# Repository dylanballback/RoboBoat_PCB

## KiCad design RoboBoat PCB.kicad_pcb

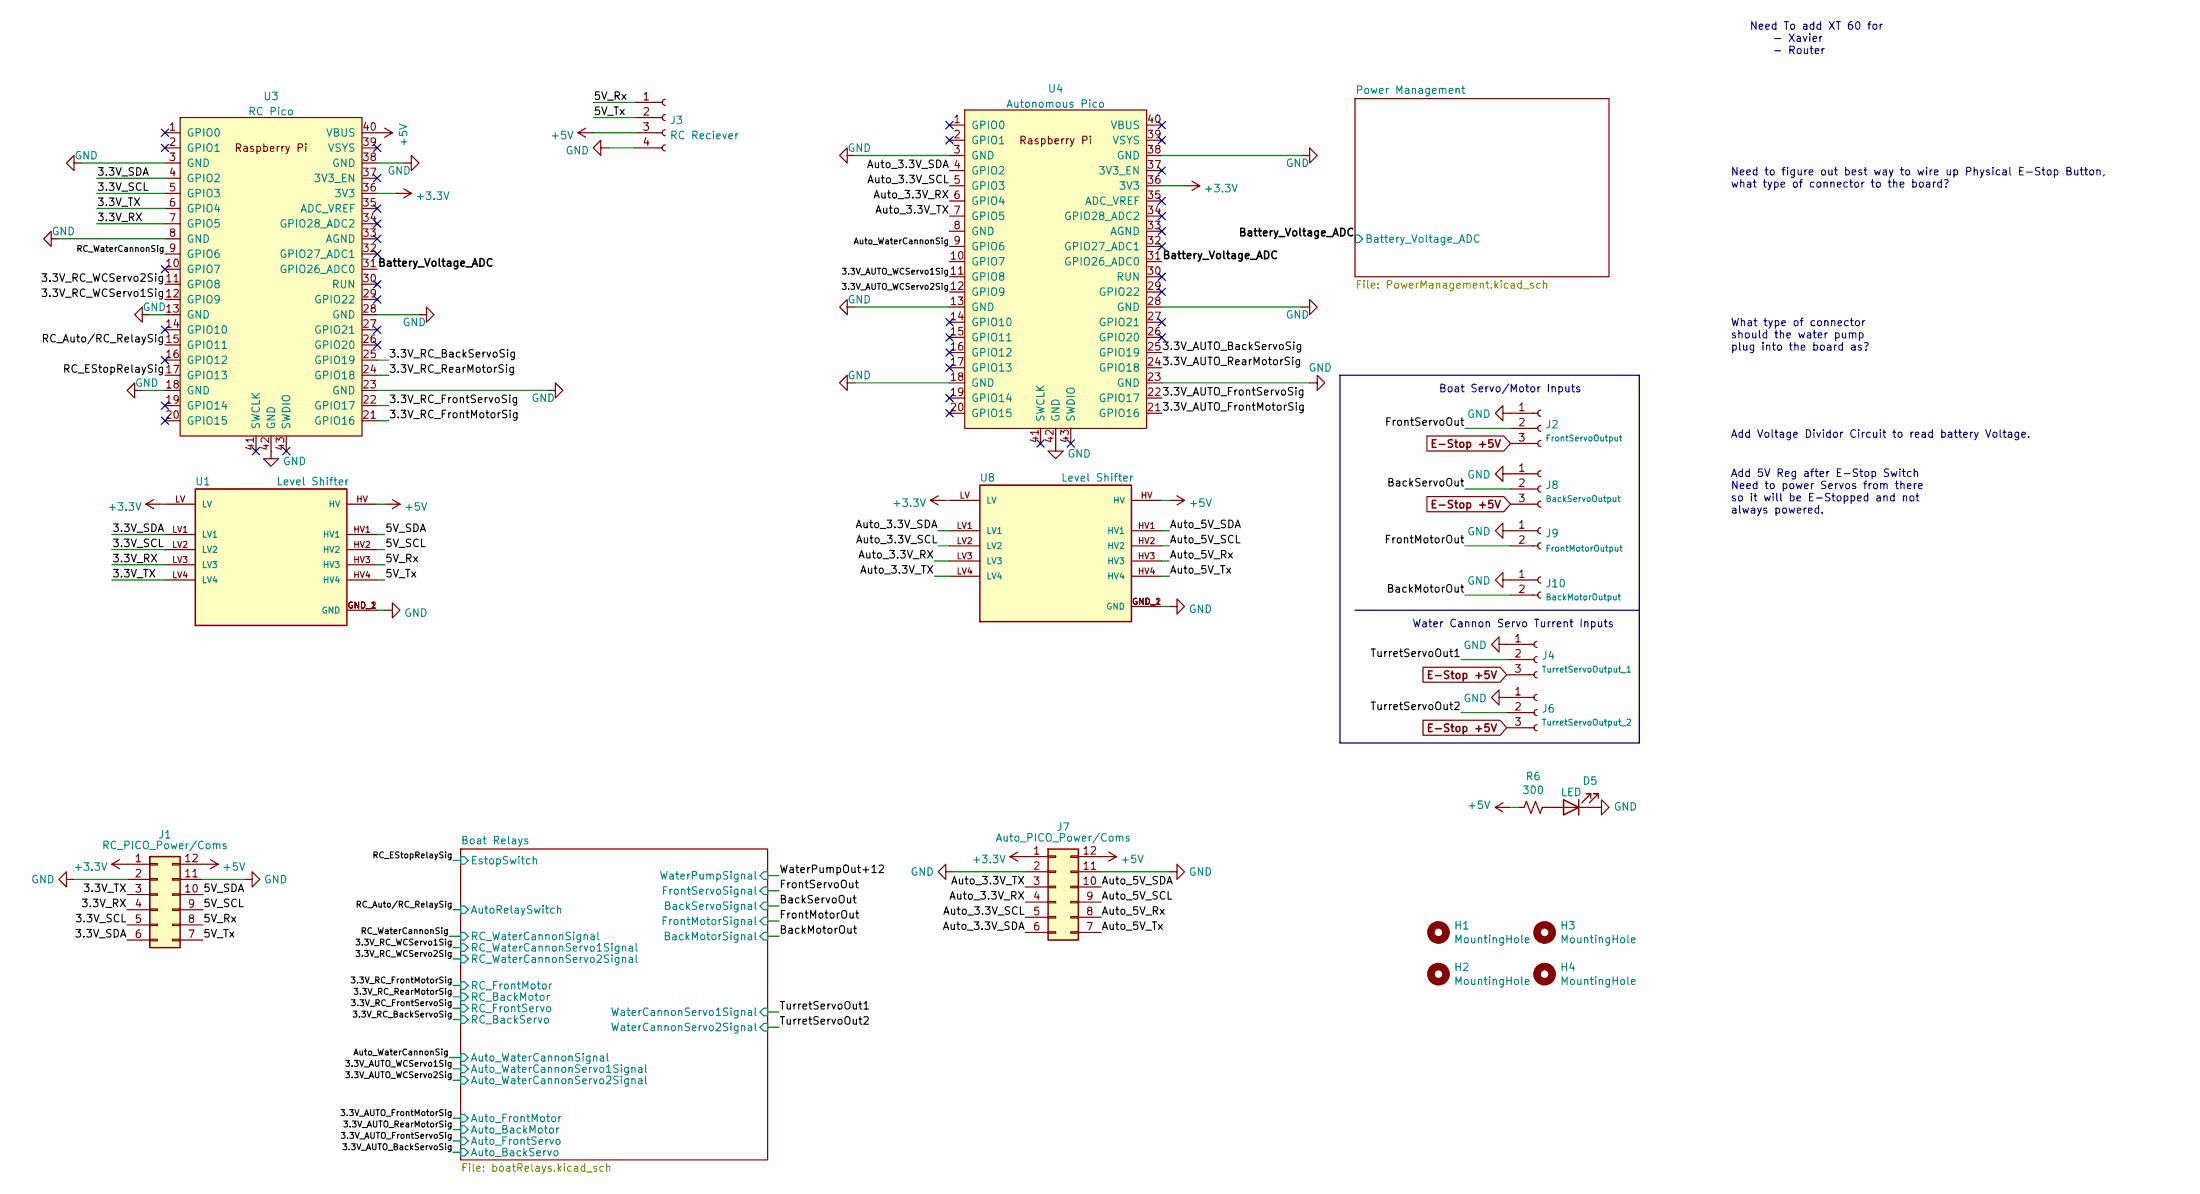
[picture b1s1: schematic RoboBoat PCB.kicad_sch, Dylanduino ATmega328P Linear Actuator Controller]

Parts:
D5: LED; LED_0402_1005Metric_Pad0.77x0.64mm_HandSolder
H1, H2, H3, H4: MountingHole; MountingHole_5.3mm_M5
J1: RC_PICO_Power/Coms; PinSocket_2x06_P2.54mm_Vertical
J2: FrontServoOutput; PinHeader_1x03_P2.54mm_Vertical
J3: RC Reciever; PinHeader_1x04_P2.54mm_Vertical
J4: TurretServoOutput_1; PinHeader_1x03_P2.54mm_Vertical
J6: TurretServoOutput_2; PinHeader_1x03_P2.54mm_Vertical
J7: Auto_PICO_Power/Coms; PinSocket_2x06_P2.54mm_Vertical
J8: BackServoOutput; PinHeader_1x03_P2.54mm_Vertical
J9: FrontMotorOutput; PinSocket_1x02_P2.54mm_Vertical
J10: BackMotorOutput; PinSocket_1x02_P2.54mm_Vertical
R6: 300; R_0805_2012Metric_Pad1.20x1.40mm_HandSolder
U1, U8: Level Shifter; CONV_BOB-12009; PARTREV 01
U3: RC Pico; RPi_Pico_SMD_TH
U4: Autonomous Pico; RPi_Pico_SMD_TH

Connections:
+3V3: J1.1, J7.1, U1.LV, U3.36 (3V3), U4.36 (3V3), U8.LV
+5V: J1.12, J3.3, J7.12, R6.2, U1.HV, U3.40 (VBUS), U8.HV; also elsewhere on the board
/3.3V_AUTO_BackServoSig: U4.25 (GPIO19); also elsewhere on the board
/3.3V_AUTO_FrontMotorSig: U4.21 (GPIO16); also elsewhere on the board
/3.3V_AUTO_FrontServoSig: U4.22 (GPIO17); also elsewhere on the board
/3.3V_AUTO_RearMotorSig: U4.24 (GPIO18); also elsewhere on the board
/3.3V_AUTO_WCServo1Sig: U4.11 (GPIO8); also elsewhere on the board
/3.3V_AUTO_WCServo2Sig: U4.12 (GPIO9); also elsewhere on the board
/3.3V_RC_BackServoSig: U3.25 (GPIO19); also elsewhere on the board
/3.3V_RC_FrontMotorSig: U3.21 (GPIO16); also elsewhere on the board
/3.3V_RC_FrontServoSig: U3.22 (GPIO17); also elsewhere on the board
/3.3V_RC_RearMotorSig: U3.24 (GPIO18); also elsewhere on the board
/3.3V_RC_WCServo1Sig: U3.12 (GPIO9); also elsewhere on the board
/3.3V_RC_WCServo2Sig: U3.11 (GPIO8); also elsewhere on the board
/3.3V_RX: J1.4, U1.LV3, U3.7 (GPIO5)
/3.3V_SCL: J1.5, U1.LV2, U3.5 (GPIO3)
/3.3V_SDA: J1.6, U1.LV1, U3.4 (GPIO2)
/3.3V_TX: J1.3, U1.LV4, U3.6 (GPIO4)
/5V_Rx: J1.8, J3.1, U1.HV3
/5V_SCL: J1.9, U1.HV2
/5V_SDA: J1.10, U1.HV1
/5V_Tx: J1.7, J3.2, U1.HV4
/Auto_3.3V_RX: J7.4, U4.6 (GPIO4), U8.LV3
/Auto_3.3V_SCL: J7.5, U4.5 (GPIO3), U8.LV2
/Auto_3.3V_SDA: J7.6, U4.4 (GPIO2), U8.LV1
/Auto_3.3V_TX: J7.3, U4.7 (GPIO5), U8.LV4
/Auto_5V_Rx: J7.8, U8.HV3
/Auto_5V_SCL: J7.9, U8.HV2
/Auto_5V_SDA: J7.10, U8.HV1
/Auto_5V_Tx: J7.7, U8.HV4
/Auto_WaterCannonSig: U4.9 (GPIO6); also elsewhere on the board
/BackMotorOut: J10.2; also elsewhere on the board
/BackServoOut: J8.2; also elsewhere on the board
/Battery_Voltage_ADC: U3.31 (GPIO26_ADC0), U4.31 (GPIO26_ADC0); also elsewhere on the board
/FrontMotorOut: J9.2; also elsewhere on the board
/FrontServoOut: J2.2; also elsewhere on the board
/RC_Auto/RC_RelaySig: U3.15 (GPIO11); also elsewhere on the board
/RC_EStopRelaySig: U3.17 (GPIO13); also elsewhere on the board
/RC_WaterCannonSig: U3.9 (GPIO6); also elsewhere on the board
/TurretServoOut1: J4.2; also elsewhere on the board
/TurretServoOut2: J6.2; also elsewhere on the board
E-Stop +5V: J2.3, J4.3, J6.3, J8.3; also elsewhere on the board
unnamed: D5.2 (A), R6.1

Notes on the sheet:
Need To add XT 60 for - Xavier - Router
Add Voltage Dividor Circuit to read battery Voltage.
Need to figure out best way to wire up Physical E-Stop Button, what type of connector to the board?
Boat Servo/Motor Inputs
What type of connector should the water pump plug into the board as?
Water Cannon Servo Turrent Inputs
Add 5V Reg after E-Stop Switch Need to power Servos from there so it will be E-Stopped and not always powered.

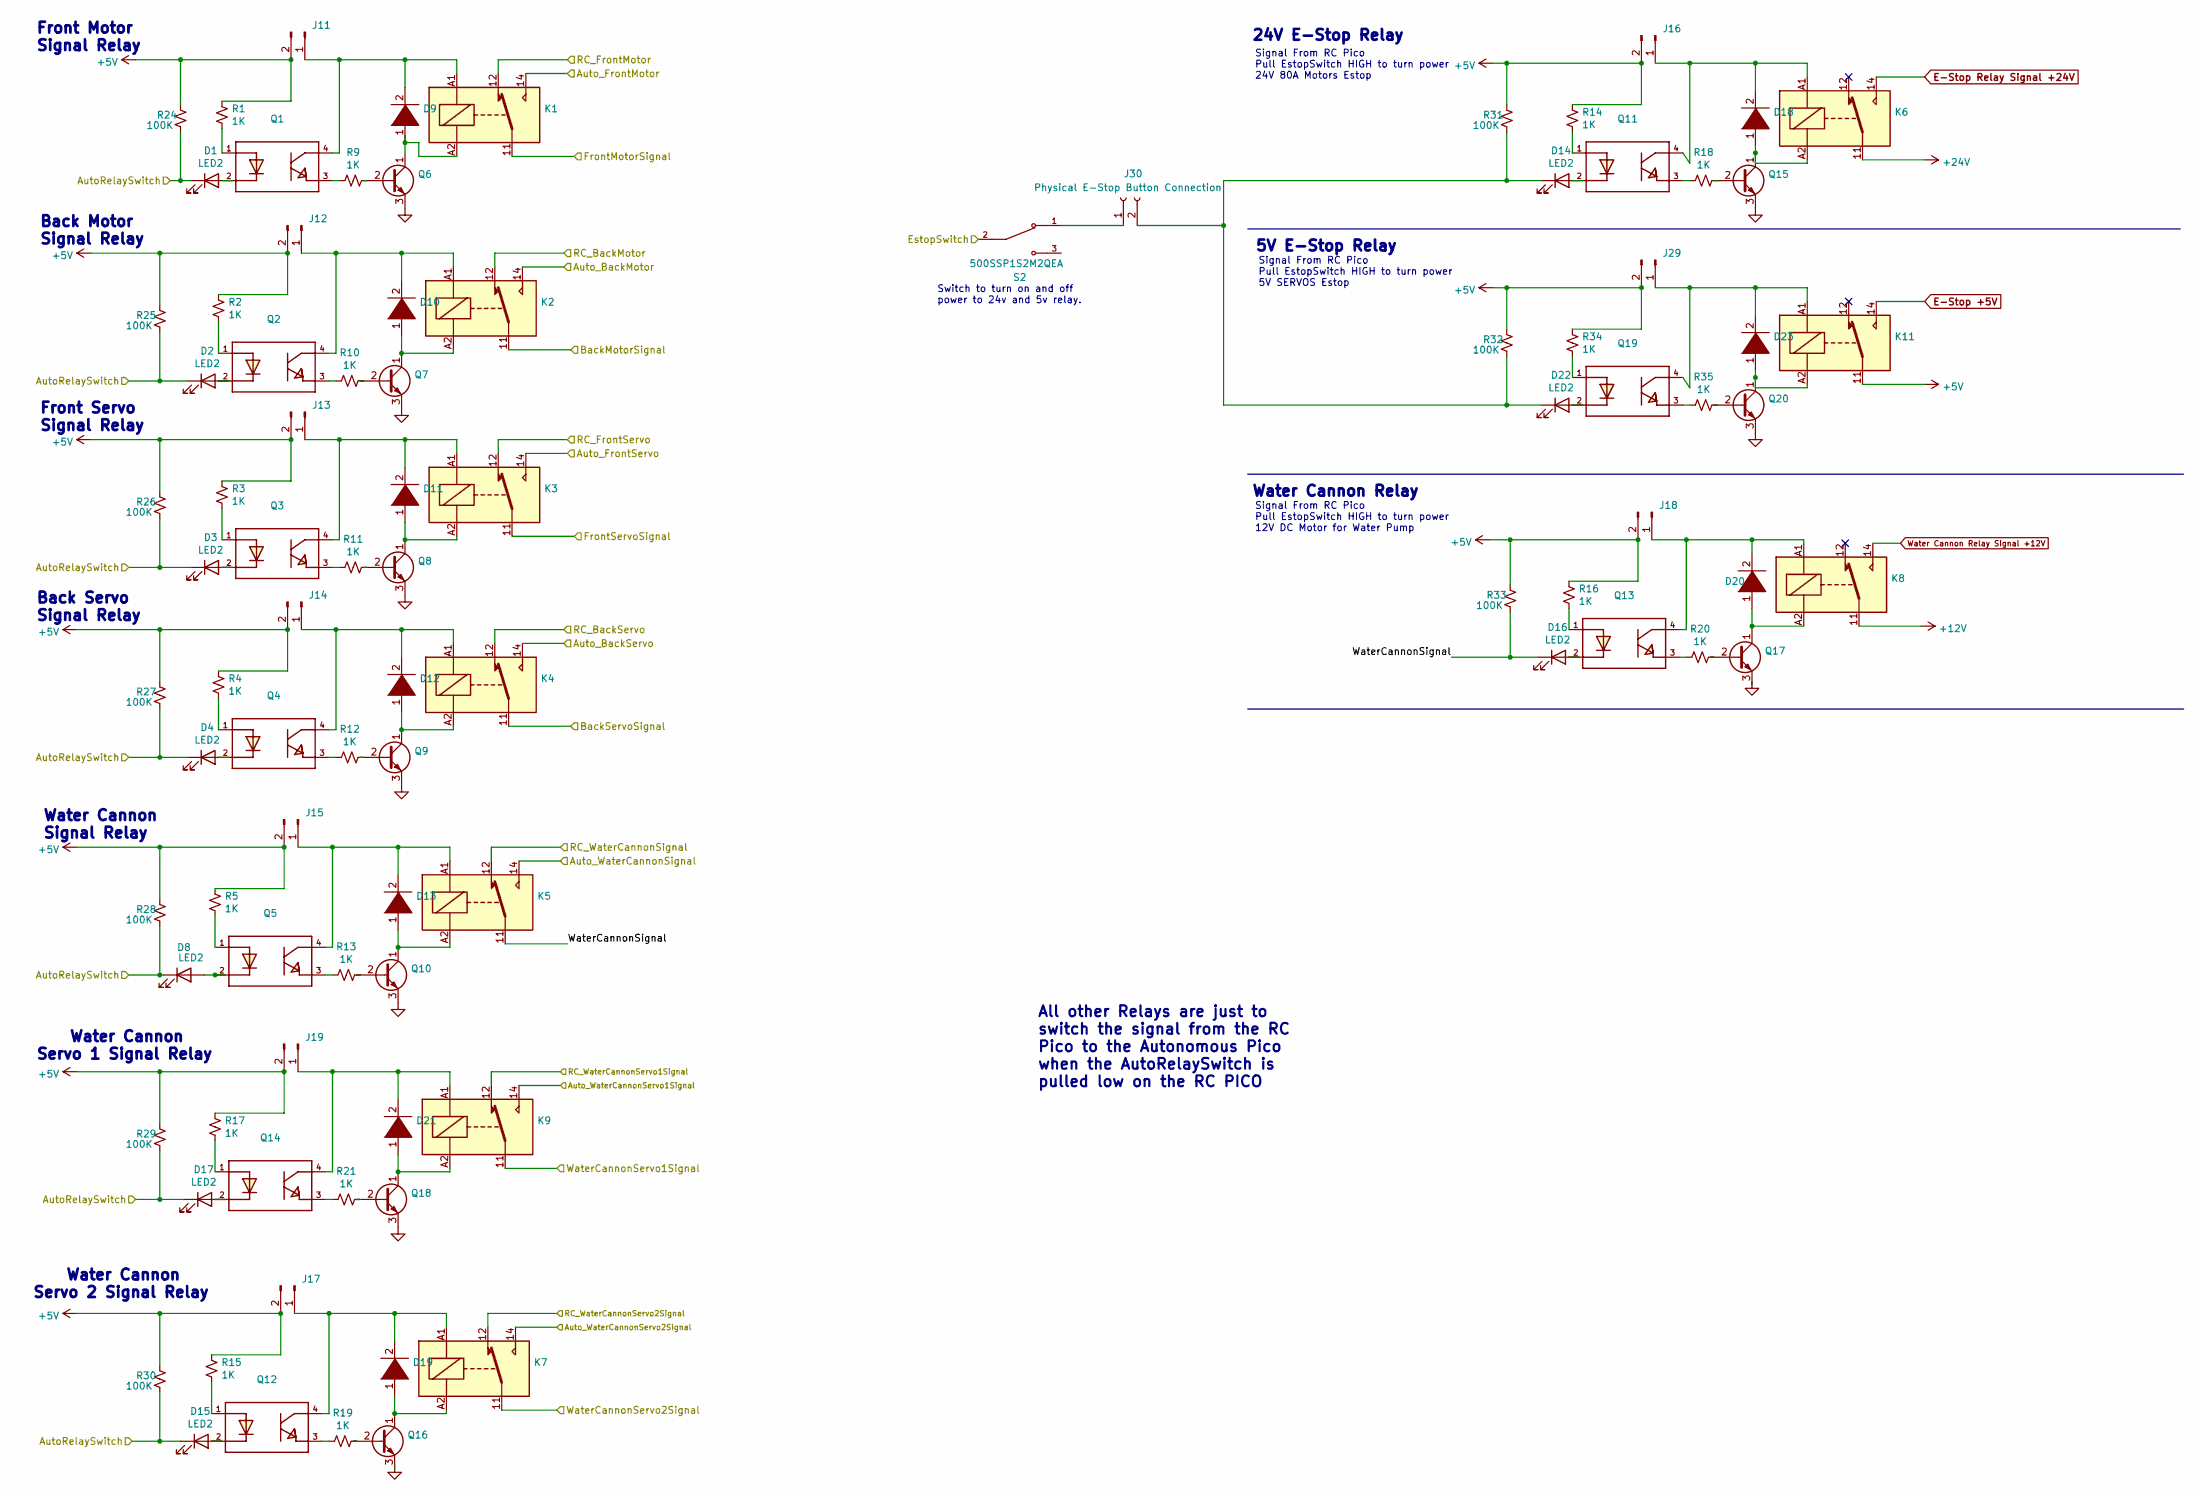
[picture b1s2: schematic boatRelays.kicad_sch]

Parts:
D1, D2, D3, D4, D8, D14, D15, D16, D17, D22: LED2; LED_0402_1005Metric_Pad0.77x0.64mm_HandSolder
D9, D10, D11, D12, D13, D18, D19, D20, D21, D23: D_1210_3225Metric_Pad1.42x2.65mm_HandSolder
J11, J12, J13, J14, J15, J16, J17, J18, J19, J29: PinHeader_1x02_P2.54mm_Vertical
J30: Physical E-Stop Button Connection; PinHeader_1x02_P2.54mm_Vertical
K1, K2, K3, K4, K5, K6, K7, K8, K9, K11: Relay_SPDT_Finder_36.11
Q1, Q2, Q3, Q4, Q5, Q11, Q12, Q13, Q14, Q19: DIP762W50P254L650H458Q4B
Q6, Q7, Q8, Q9, Q10, Q15, Q16, Q17, Q18, Q20: TO-92_Inline
R1, R2, R3, R4, R5, R9, R10, R11, R12, R13, R14, R15, R16, R17, R18, R19, R20, R21, R34, R35: 1K; R_0805_2012Metric_Pad1.20x1.40mm_HandSolder
R24, R25, R26, R27, R28, R29, R30, R31, R32, R33: 100K; R_0805_2012Metric_Pad1.20x1.40mm_HandSolder
S2: 500SSP1S2M2QEA; SW_500SSP1S2M2QEA; PARTREV C

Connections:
+5V: J11.2, J12.2, J13.2, J14.2, J15.2, J16.2, J17.2, J18.2, J19.2, J29.2, K11.11, R1.1, R2.1, R3.1, R4.1, R5.1, R14.1, R15.1, R16.1, R17.1, R24.1, R25.1, R26.1, R27.1, R28.1, R29.1, R30.1, R31.1, R32.1, R33.1, R34.1; also elsewhere on the board
+12V: K8.11; also elsewhere on the board
+24V: K6.11; also elsewhere on the board
/3.3V_AUTO_BackServoSig: K4.14; also elsewhere on the board
/3.3V_AUTO_FrontMotorSig: K1.14; also elsewhere on the board
/3.3V_AUTO_FrontServoSig: K3.14; also elsewhere on the board
/3.3V_AUTO_RearMotorSig: K2.14; also elsewhere on the board
/3.3V_AUTO_WCServo1Sig: K9.14; also elsewhere on the board
/3.3V_AUTO_WCServo2Sig: K7.14; also elsewhere on the board
/3.3V_RC_BackServoSig: K4.12; also elsewhere on the board
/3.3V_RC_FrontMotorSig: K1.12; also elsewhere on the board
/3.3V_RC_FrontServoSig: K3.12; also elsewhere on the board
/3.3V_RC_RearMotorSig: K2.12; also elsewhere on the board
/3.3V_RC_WCServo1Sig: K9.12; also elsewhere on the board
/3.3V_RC_WCServo2Sig: K7.12; also elsewhere on the board
/Auto_WaterCannonSig: K5.14; also elsewhere on the board
/BackMotorOut: K2.11; also elsewhere on the board
/BackServoOut: K4.11; also elsewhere on the board
/Boat Relays/WaterCannonSignal: D16.1 (K), K5.11, R33.2
/FrontMotorOut: K1.11; also elsewhere on the board
/FrontServoOut: K3.11; also elsewhere on the board
/RC_Auto/RC_RelaySig: D1.1 (K), D2.1 (K), D3.1 (K), D4.1 (K), D8.1 (K), D15.1 (K), D17.1 (K), R24.2, R25.2, R26.2, R27.2, R28.2, R29.2, R30.2; also elsewhere on the board
/RC_EStopRelaySig: S2.2; also elsewhere on the board
/RC_WaterCannonSig: K5.12; also elsewhere on the board
/TurretServoOut1: K9.11; also elsewhere on the board
/TurretServoOut2: K7.11; also elsewhere on the board
E-Stop +5V: K11.14; also elsewhere on the board
E-Stop Relay Signal +24V: K6.14; also elsewhere on the board
unnamed: D1.2 (A), Q1.2
unnamed: D2.2 (A), Q2.2
unnamed: D3.2 (A), Q3.2
unnamed: D4.2 (A), Q4.2
unnamed: D8.2 (A), Q5.2
unnamed: D9.1 (K), K1.A2, Q6.1 (C)
unnamed: D9.2 (A), J11.1, K1.A1, Q1.4
unnamed: D10.1 (K), K2.A2, Q7.1 (C)
unnamed: D10.2 (A), J12.1, K2.A1, Q2.4
unnamed: D11.1 (K), K3.A2, Q8.1 (C)
unnamed: D11.2 (A), J13.1, K3.A1, Q3.4
unnamed: D12.1 (K), K4.A2, Q9.1 (C)
unnamed: D12.2 (A), J14.1, K4.A1, Q4.4
unnamed: D13.1 (K), K5.A2, Q10.1 (C)
unnamed: D13.2 (A), J15.1, K5.A1, Q5.4
unnamed: D14.1 (K), D22.1 (K), J30.2, R31.2, R32.2
unnamed: D14.2 (A), Q11.2
unnamed: D15.2 (A), Q12.2
unnamed: D16.2 (A), Q13.2
unnamed: D17.2 (A), Q14.2
unnamed: D18.1 (K), K6.A2, Q15.1 (C)
unnamed: D18.2 (A), J16.1, K6.A1, Q11.4
unnamed: D19.1 (K), K7.A2, Q16.1 (C)
unnamed: D19.2 (A), J17.1, K7.A1, Q12.4
unnamed: D20.1 (K), K8.A2, Q17.1 (C)
unnamed: D20.2 (A), J18.1, K8.A1, Q13.4
unnamed: D21.1 (K), K9.A2, Q18.1 (C)
unnamed: D21.2 (A), J19.1, K9.A1, Q14.4
unnamed: D22.2 (A), Q19.2
unnamed: D23.1 (K), K11.A2, Q20.1 (C)
unnamed: D23.2 (A), J29.1, K11.A1, Q19.4
unnamed: Q1.1, R1.2
unnamed: Q1.3, R9.2
unnamed: Q2.1, R2.2
unnamed: Q2.3, R10.2
unnamed: Q3.1, R3.2
unnamed: Q3.3, R11.2
unnamed: Q4.1, R4.2
unnamed: Q4.3, R12.2
unnamed: Q5.1, R5.2
unnamed: Q5.3, R13.2
unnamed: Q6.2 (B), R9.1
unnamed: Q7.2 (B), R10.1
unnamed: Q8.2 (B), R11.1
unnamed: Q9.2 (B), R12.1
unnamed: Q10.2 (B), R13.1
unnamed: Q11.1, R14.2
unnamed: Q11.3, R18.2
unnamed: Q12.1, R15.2
unnamed: Q12.3, R19.2
unnamed: Q13.1, R16.2
unnamed: Q13.3, R20.2
unnamed: Q14.1, R17.2
unnamed: Q14.3, R21.2
unnamed: Q15.2 (B), R18.1
unnamed: Q16.2 (B), R19.1
unnamed: Q17.2 (B), R20.1
unnamed: Q18.2 (B), R21.1
unnamed: Q19.1, R34.2
unnamed: Q19.3, R35.2
unnamed: Q20.2 (B), R35.1
unnamed: J30.1, S2.1
Water Cannon Relay Signal +12V: K8.14; also elsewhere on the board

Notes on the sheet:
5V E-Stop Relay
All other Relays are just to switch the signal from the RC Pico to the Autonomous Pico when the AutoRelaySwitch is pulled low on the RC PICO
Front Motor Signal Relay
Switch to turn on and off power to 24v and 5v relay.
Water Cannon Servo 1 Signal Relay
Water Cannon Servo 2 Signal Relay
Front Servo Signal Relay
Signal From RC Pico Pull EstopSwitch HIGH to turn power 5V SERVOS Estop
24V E-Stop Relay
Back Motor Signal Relay
Water Cannon Relay
Back Servo Signal Relay
Water Cannon Signal Relay
Signal From RC Pico Pull EstopSwitch HIGH to turn power 24V 80A Motors Estop
Signal From RC Pico Pull EstopSwitch HIGH to turn power 12V DC Motor for Water Pump

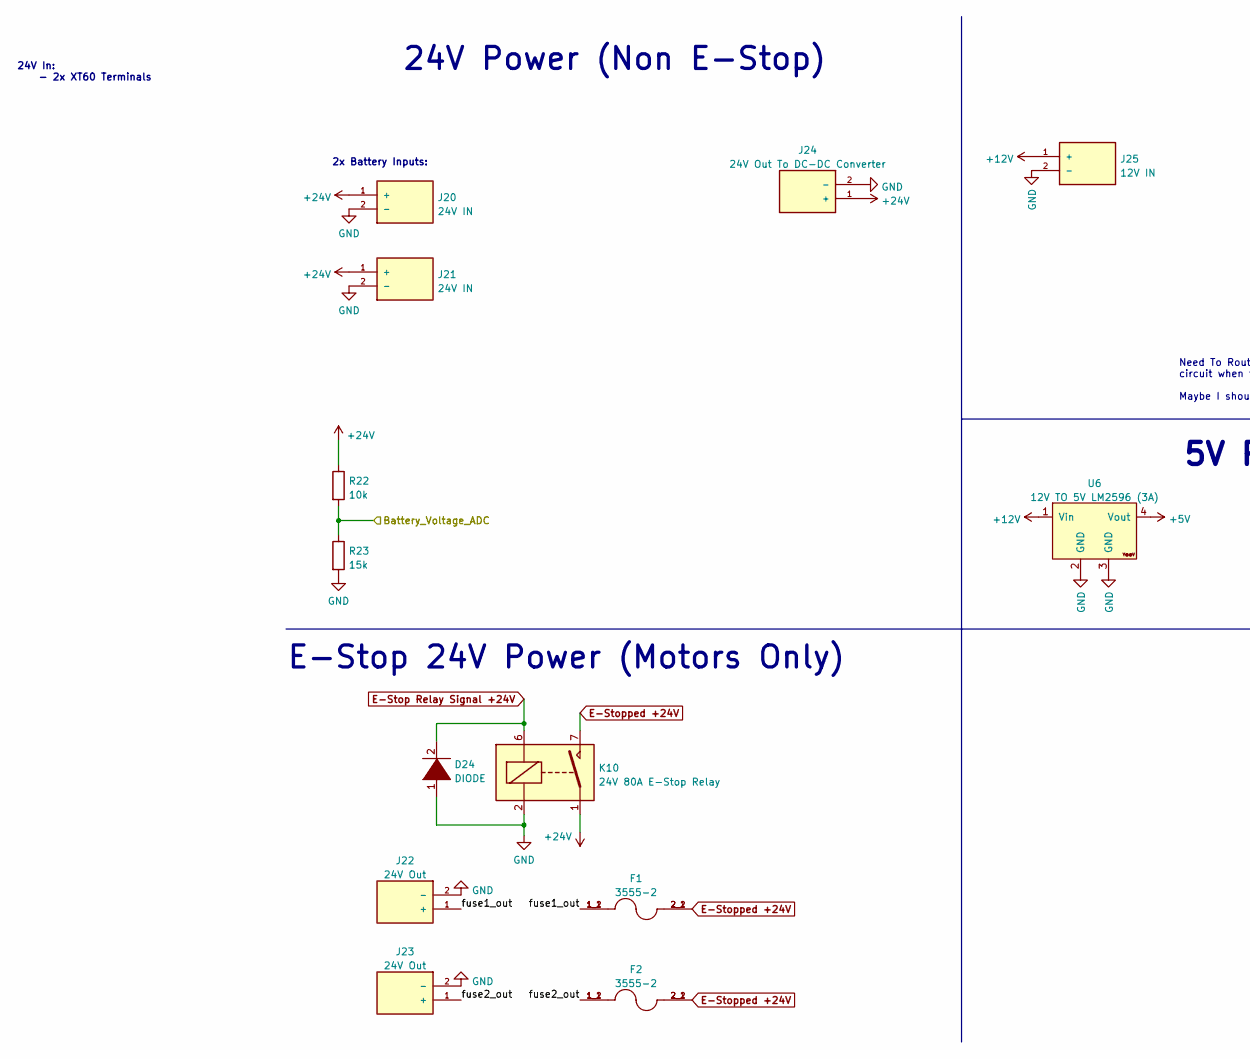
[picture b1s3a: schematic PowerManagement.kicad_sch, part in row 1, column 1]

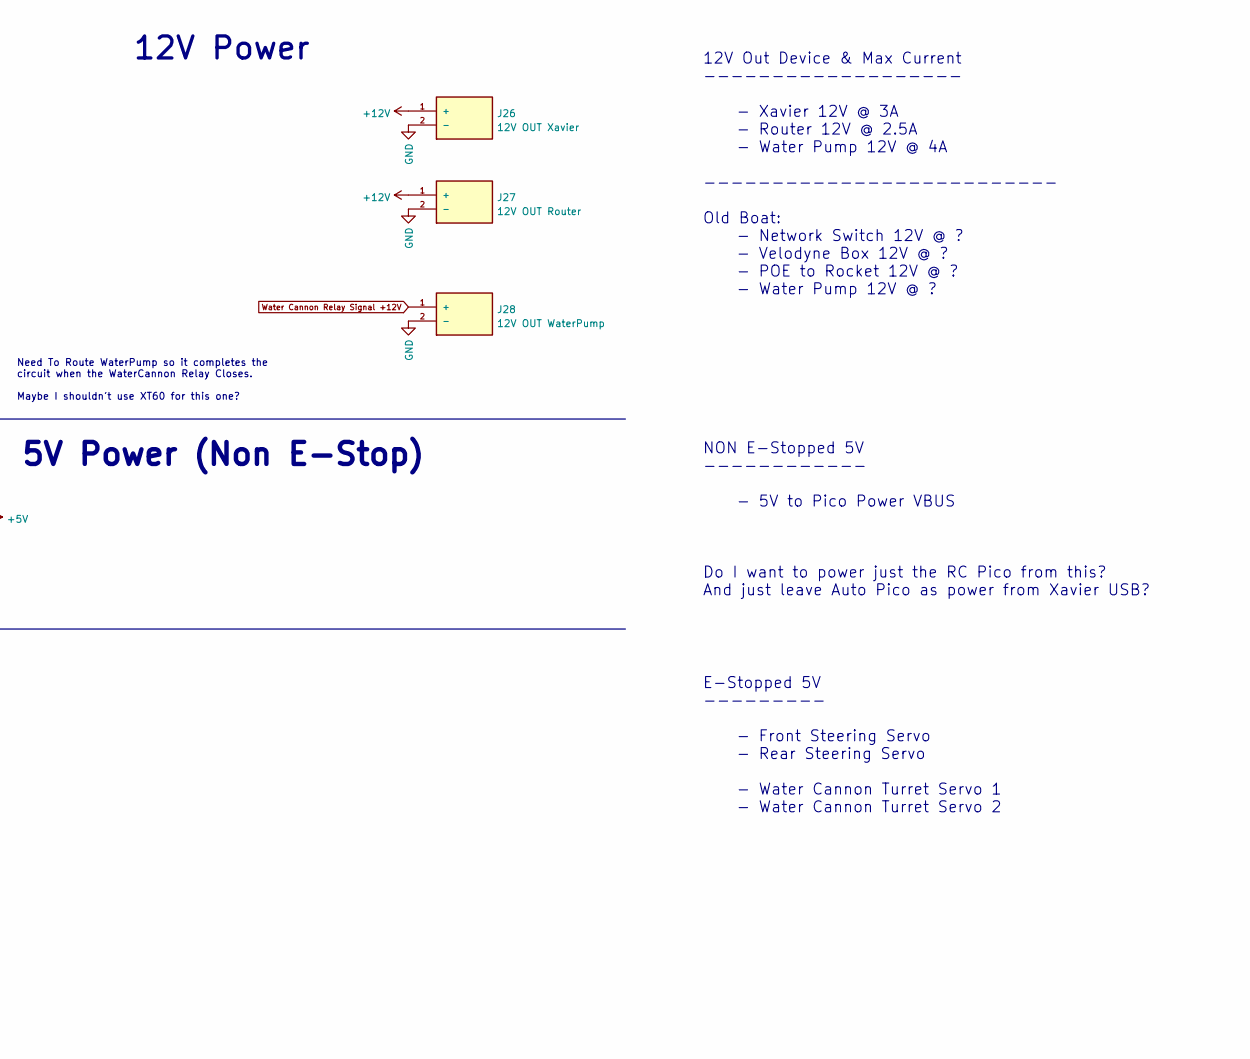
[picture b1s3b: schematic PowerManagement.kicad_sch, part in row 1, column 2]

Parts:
D24: DIODE; D_3220_8050Metric_Pad2.65x5.15mm_HandSolder
F1, F2: 3555-2; FUSE_3555-2; PARTREV A
J20, J21: 24V IN; AMASS_XT60PW-M; PARTREV V1.2
J22, J23: 24V Out; AMASS_XT60PW-M; PARTREV V1.2
J24: 24V Out To DC-DC Converter; AMASS_XT60PW-M; PARTREV V1.2
J25: 12V IN; AMASS_XT60PW-M; PARTREV V1.2
J26: 12V OUT Xavier; AMASS_XT60PW-M; PARTREV V1.2
J27: 12V OUT Router; AMASS_XT60PW-M; PARTREV V1.2
J28: 12V OUT WaterPump; AMASS_XT60PW-M; PARTREV V1.2
K10: 24V 80A E-Stop Relay; JD2912-1H-24VDC 80A 28VDC
R22: 10k; R_0805_2012Metric_Pad1.20x1.40mm_HandSolder
R23: 15k; R_0805_2012Metric_Pad1.20x1.40mm_HandSolder
U6: 12V TO 5V LM2596 (3A); DCDC_StepDown_LM2596

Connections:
+5V: U6.4 (Vout); also elsewhere on the board
+12V: J25.1 (+), J26.1 (+), J27.1 (+), U6.1 (Vin); also elsewhere on the board
+24V: J20.1 (+), J21.1 (+), J24.1 (+), K10.1, K10.14, R22.1; also elsewhere on the board
/Battery_Voltage_ADC: R22.2, R23.1; also elsewhere on the board
/Power Management/fuse1_out: F1.1_1, F1.1_2, J22.1 (+)
/Power Management/fuse2_out: F2.1_1, F2.1_2, J23.1 (+)
E-Stop Relay Signal +24V: D24.2 (A), K10.6; also elsewhere on the board
E-Stopped +24V: F1.2_1, F1.2_2, F2.2_1, F2.2_2, K10.7, K10.8
Water Cannon Relay Signal +12V: J28.1 (+); also elsewhere on the board

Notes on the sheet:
12V Out Device & Max Current ------------------- - Xavier 12V @ 3A - Router 12V @ 2.5A - Water Pump 12V @ 4A -------------------------- Old Boat: - Network Switch 12V @ ? - Velodyne Box 12V @ ? - POE to Rocket 12V @ ? - Water Pump 12V @ ?
24V Power (Non E-Stop)
2x Battery Inputs:
12V Power
Need To Route WaterPump so it completes the circuit when the WaterCannon Relay Closes. Maybe I shouldn't use XT60 for this one?
24V In: - 2x XT60 Terminals
NON E-Stopped 5V ------------ - 5V to Pico Power VBUS Do I want to power just the RC Pico from this? And just leave Auto Pico as power from Xavier USB?
E-Stop 24V Power (Motors Only)
E-Stopped 5V --------- - Front Steering Servo - Rear Steering Servo - Water Cannon Turret Servo 1 - Water Cannon Turret Servo 2
5V Power (Non E-Stop)

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
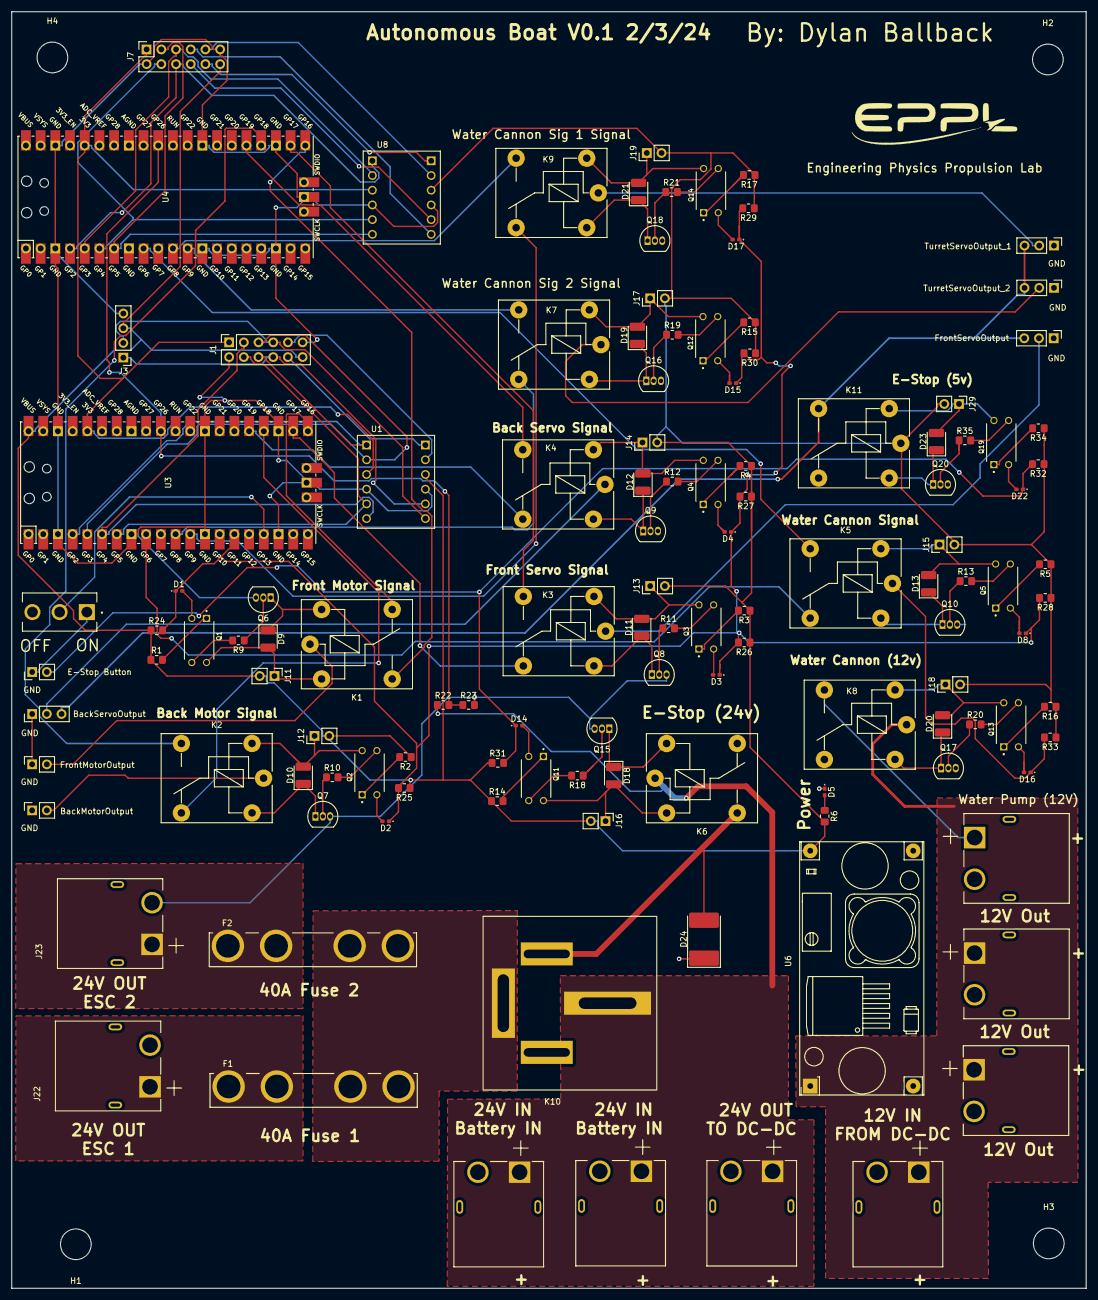
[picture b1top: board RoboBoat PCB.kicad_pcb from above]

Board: 2 copper layers, 185.6 x 220.5 mm, 127 parts (0 on the bottom side), 114 nets.
